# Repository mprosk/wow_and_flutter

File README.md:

# Wow & Flutter
Wow &amp; Flutter is a pitch modulation source designed to emulate the nostalgic warbles of a aged tape deck.

Output is selectable between triangle or random sample and hold with slew. A jumper on the back of the module sets three different output levels

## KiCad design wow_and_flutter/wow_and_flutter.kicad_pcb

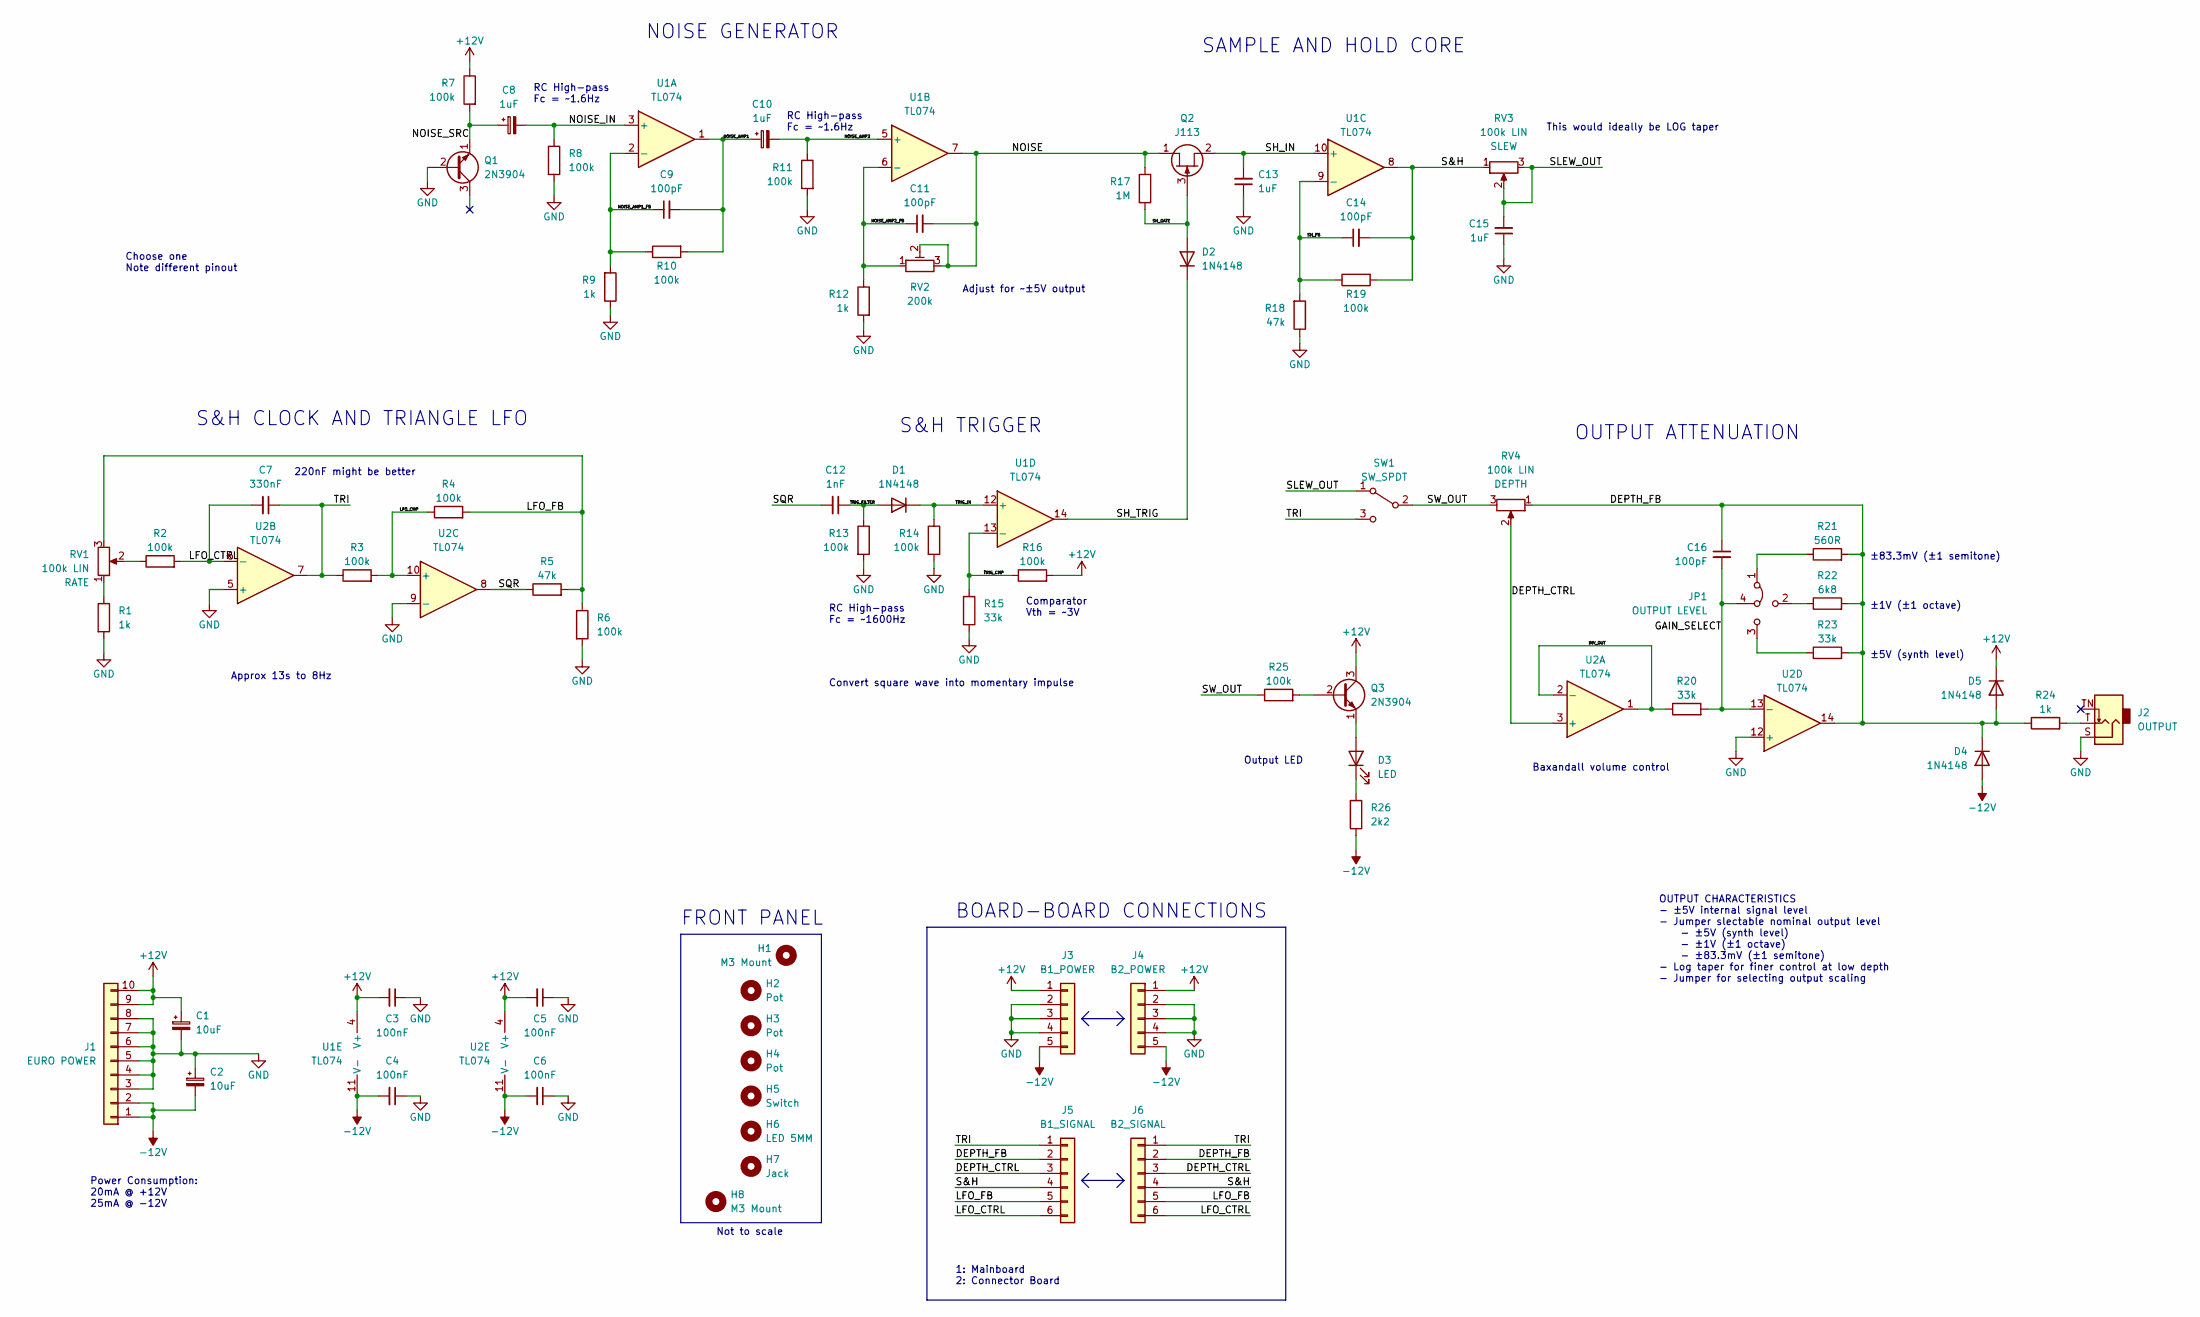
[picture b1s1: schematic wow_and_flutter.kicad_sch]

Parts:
C1, C2: 10uF; CP_Radial_D4.0mm_P1.50mm
C3, C4, C5, C6: 100nF; C_Disc_D3.0mm_W1.6mm_P2.50mm
C7: 330nF; C_Disc_D3.0mm_W1.6mm_P2.50mm
C8, C10: 1uF; CP_Radial_D4.0mm_P1.50mm
C9, C11, C14, C16: 100pF; C_Disc_D3.0mm_W1.6mm_P2.50mm
C12: 1nF; C_Disc_D3.0mm_W1.6mm_P2.50mm
C13, C15: 1uF; C_Disc_D3.0mm_W1.6mm_P2.50mm
D1, D2, D4, D5: 1N4148; D_DO-34_SOD68_P7.62mm_Horizontal
D3: LED; LED_D5.0mm
H1, H8: M3 Mount; MountingHole_3.2mm_M3
H2, H3, H4: Pot; Hole_Pot
H5: Switch; Hole_Toggle_Switch
H6: LED 5MM; Hole_LED_5mm
H7: Jack; Hole_Jack_3.5mm
J1: EURO POWER; IDC-Header_2x05_P2.54mm_Vertical
J2: OUTPUT; Jack_3.5mm_QingPu_WQP-PJ301BM
J3: B1_POWER; PinHeader_1x05_P2.54mm_Vertical
J4: B2_POWER; PinSocket_1x05_P2.54mm_Vertical
J5: B1_SIGNAL; PinHeader_1x06_P2.54mm_Vertical
J6: B2_SIGNAL; PinSocket_1x06_P2.54mm_Vertical
JP1: OUTPUT LEVEL; Jumper_3_to_1
Q1, Q3: 2N3904; TO-92_Inline
Q2: J113; TO-92_Inline
R1, R9, R12, R24: 1k; R_Axial_DIN0207_L6.3mm_D2.5mm_P10.16mm_Horizontal
R2, R3, R4, R6, R7, R8, R10, R11, R13, R14, R16, R19, R25: 100k; R_Axial_DIN0207_L6.3mm_D2.5mm_P10.16mm_Horizontal
R5, R18: 47k; R_Axial_DIN0207_L6.3mm_D2.5mm_P10.16mm_Horizontal
R15, R20, R23: 33k; R_Axial_DIN0207_L6.3mm_D2.5mm_P10.16mm_Horizontal
R17: 1M; R_Axial_DIN0207_L6.3mm_D2.5mm_P10.16mm_Horizontal
R21: 560R; R_Axial_DIN0207_L6.3mm_D2.5mm_P10.16mm_Horizontal
R22: 6k8; R_Axial_DIN0207_L6.3mm_D2.5mm_P10.16mm_Horizontal
R26: 2k2; R_Axial_DIN0207_L6.3mm_D2.5mm_P10.16mm_Horizontal
RV1, RV3, RV4: 100k LIN; Potentiometer_TT_P0915N
RV2: 200k; Potentiometer_Trim_Horizontal
SW1: SW_SPDT; Switch_SPDT
U1, U2: TL074; DIP-14_W7.62mm

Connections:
+12V: C1.1, C3.2, C5.2, D5.1 (K), J1.9, J1.10, J3.1, J4.1, Q3.3 (C), R7.1, R16.2, U1.4 (V+), U2.4 (V+)
-12V: C2.2, C4.2, C6.2, D4.2 (A), J1.1, J1.2, J3.5, J4.5, R26.1, U1.11 (V-), U2.11 (V-)
/DEPTH_CTRL: J5.3, J6.3, RV4.2, U2.3 (+)
/DEPTH_FB: C16.1, D4.1 (K), D5.2 (A), J5.2, J6.2, R21.2, R22.2, R23.2, R24.1, RV4.1, U2.14
/GAIN_SELECT: C16.2, JP1.4 (C), R20.2, U2.13 (-)
/INV_OUT: R20.1, U2.1, U2.2 (-)
/LFO_CMP: R3.2, R4.1, U2.10 (+)
/LFO_CTRL: C7.2, J5.6, J6.6, R2.2, U2.6 (-)
/LFO_FB: J5.5, J6.5, R4.2, R5.2, R6.1, RV1.3
/NOISE: C11.2, Q2.1 (D), R17.1, RV2.2, RV2.3, U1.7
/NOISE_AMP1: C9.2, C10.1, R10.2, U1.1
/NOISE_AMP1_FB: C9.1, R9.2, R10.1, U1.2 (-)
/NOISE_AMP2: C10.2, R11.1, U1.5 (+)
/NOISE_AMP2_FB: C11.1, R12.1, RV2.1, U1.6 (-)
/NOISE_IN: C8.2, R8.1, U1.3 (+)
/NOISE_SRC: C8.1, Q1.1 (E), R7.2
/S&H: C14.2, J5.4, J6.4, R19.2, RV3.1, U1.8
/SH_FB: C14.1, R18.2, R19.1, U1.9 (-)
/SH_GATE: D2.2 (A), Q2.3 (G), R17.2
/SH_IN: C13.2, Q2.2 (S), U1.10 (+)
/SH_TRIG: D2.1 (K), U1.14
/SLEW_OUT: C15.2, RV3.2, RV3.3, SW1.1 (A)
/SQR: C12.2, R5.1, U2.8
/SW_OUT: R25.1, RV4.3, SW1.2 (B)
/TRI: C7.1, J5.1, J6.1, R3.1, SW1.3 (C), U2.7
/TRIG_CMP: R15.2, R16.1, U1.13 (-)
/TRIG_FILTER: C12.1, D1.2 (A), R13.1
/TRIG_IN: D1.1 (K), R14.1, U1.12 (+)
GND: C1.2, C2.1, C3.1, C4.1, C5.1, C6.1, C13.1, C15.1, J1.3, J1.4, J1.5, J1.6, J1.7, J1.8, J2.S, J3.2, J3.3, J3.4, J4.2, J4.3, J4.4, Q1.2 (B), R1.2, R6.2, R8.2, R9.1, R11.2, R12.2, R13.2, R14.2, R15.1, R18.1, U2.5 (+), U2.9 (-), U2.12 (+)
unnamed: D3.1 (K), R26.2
unnamed: D3.2 (A), Q3.1 (E)
unnamed: J2.T, R24.2
unnamed: JP1.1 (A), R21.1
unnamed: JP1.2 (C), R22.1
unnamed: JP1.3 (B), R23.1
unnamed: Q3.2 (B), R25.2
unnamed: R1.1, RV1.1
unnamed: R2.1, RV1.2

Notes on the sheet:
Power Consumption: 20mA @ +12V 25mA @ -12V
OUTPUT CHARACTERISTICS - ±5V internal signal level - Jumper slectable nominal output level - ±5V (synth level) - ±1V (±1 octave) - ±83.3mV (±1 semitone) - Log taper for finer control at low depth - Jumper for selecting output scaling
Not to scale
This would ideally be LOG taper
Choose one Note different pinout
±5V (synth level)
NOISE GENERATOR
RC High-pass Fc = ~1.6Hz
Approx 13s to 8Hz
Output LED
RC High-pass Fc = ~1600Hz
±83.3mV (±1 semitone)
S&H TRIGGER
Convert square wave into momentary impulse
1: Mainboard 2: Connector Board
220nF might be better
±1V (±1 octave)
OUTPUT ATTENUATION
Adjust for ~±5V output
Baxandall volume control
FRONT PANEL
BOARD-BOARD CONNECTIONS
S&H CLOCK AND TRIANGLE LFO
Comparator Vth = ~3V
SAMPLE AND HOLD CORE

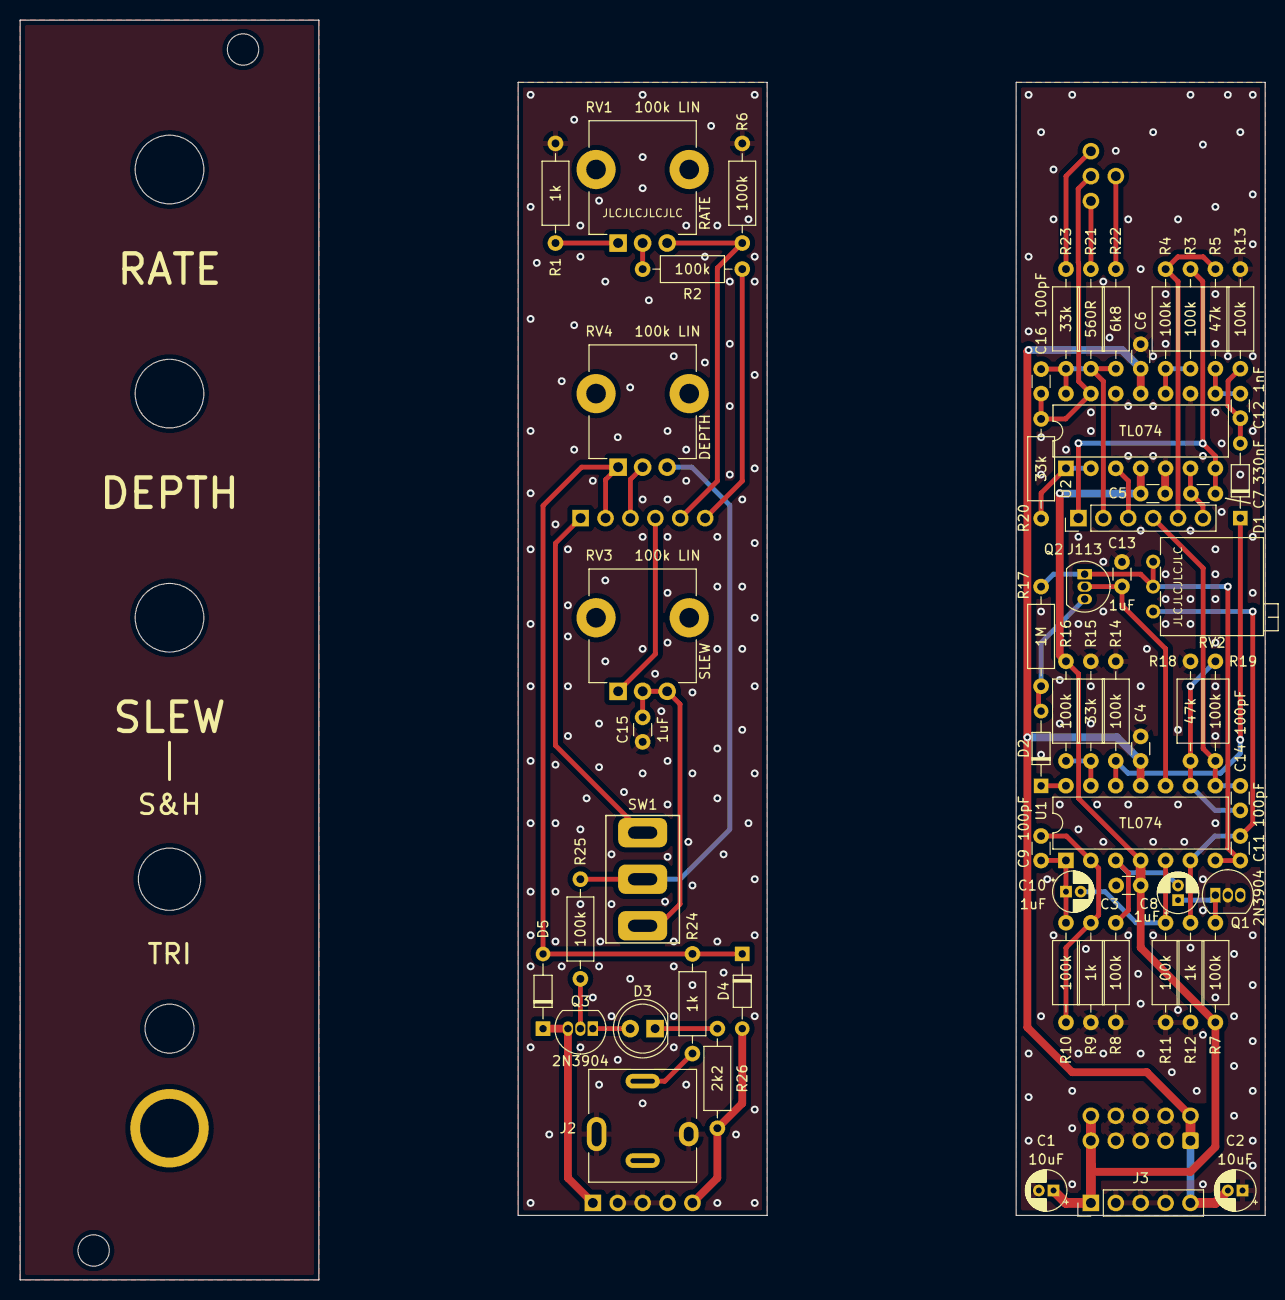
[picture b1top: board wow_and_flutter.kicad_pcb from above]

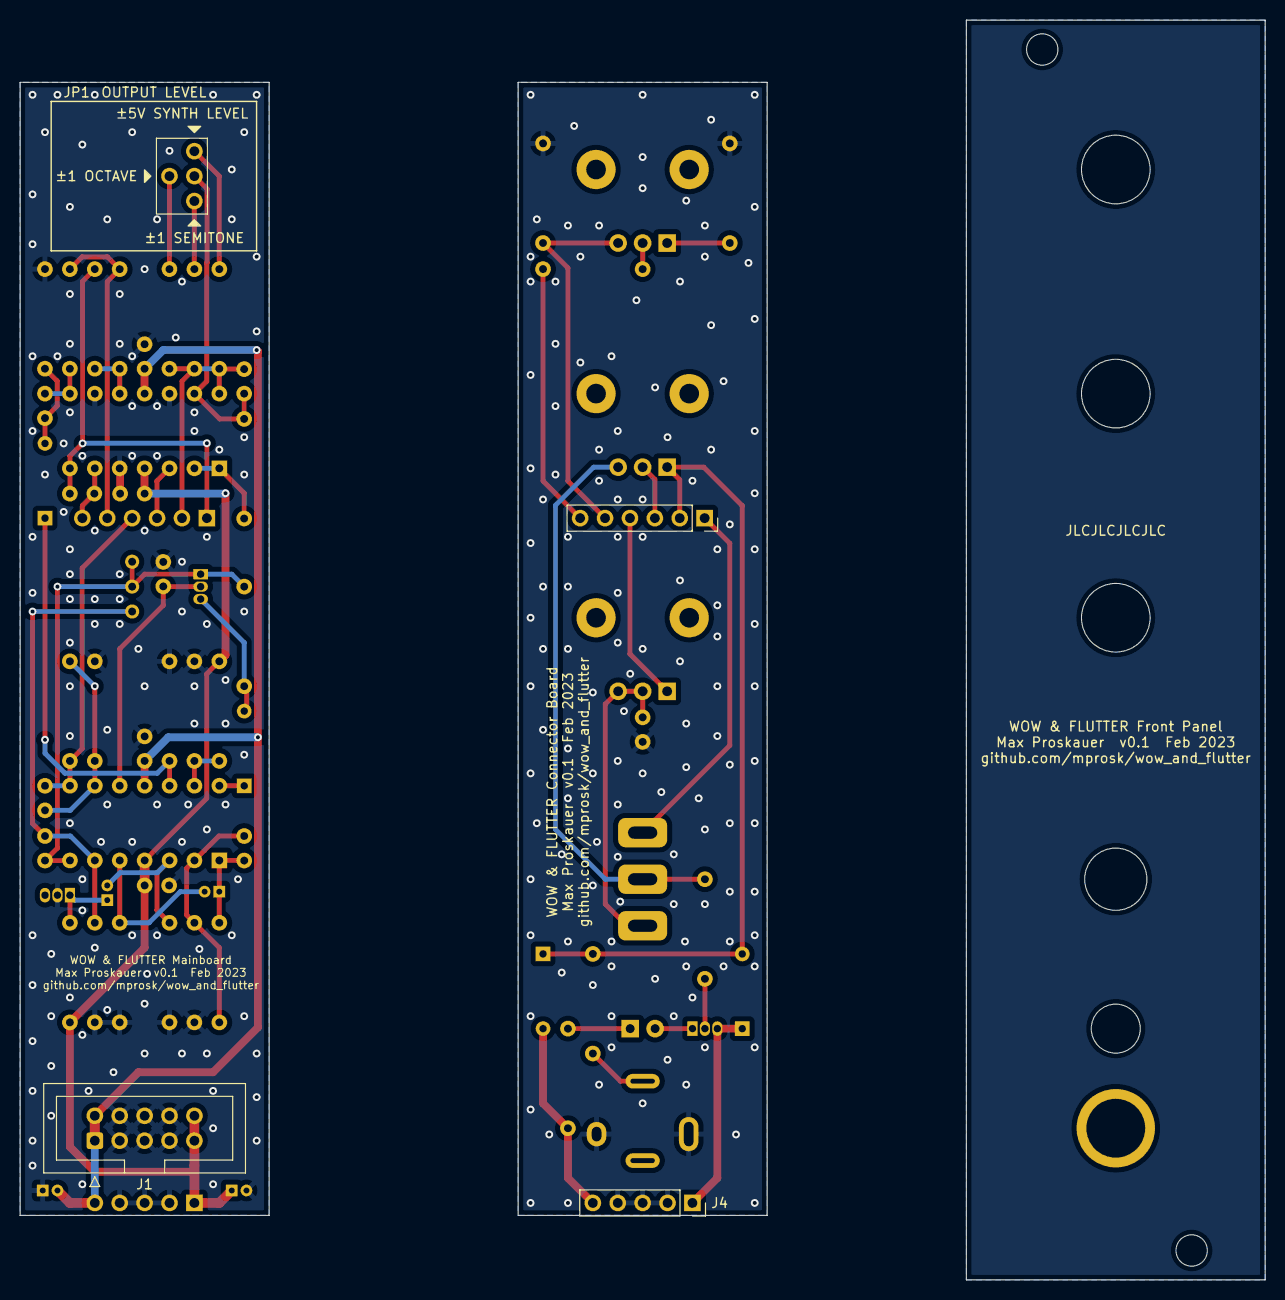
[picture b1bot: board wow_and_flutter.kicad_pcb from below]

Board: 2 copper layers, 127.0 x 128.5 mm, 72 parts (4 on the bottom side), 38 nets.

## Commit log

2023-02-15 Complete PCB laout
2023-02-15 Add version info to PCBs
2023-12-20 Add list of issues on schematic
